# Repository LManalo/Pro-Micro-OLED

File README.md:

# Pro-Micro-OLED
An Atmega32u4-based development board with an onboard OLED display connected to pins D2-D7 and the I2C bus.

Designed during my time at Sparkfun Electronics, and the board design is based off the Sparkfun Pro Micro and Lilypad Arduino USB.

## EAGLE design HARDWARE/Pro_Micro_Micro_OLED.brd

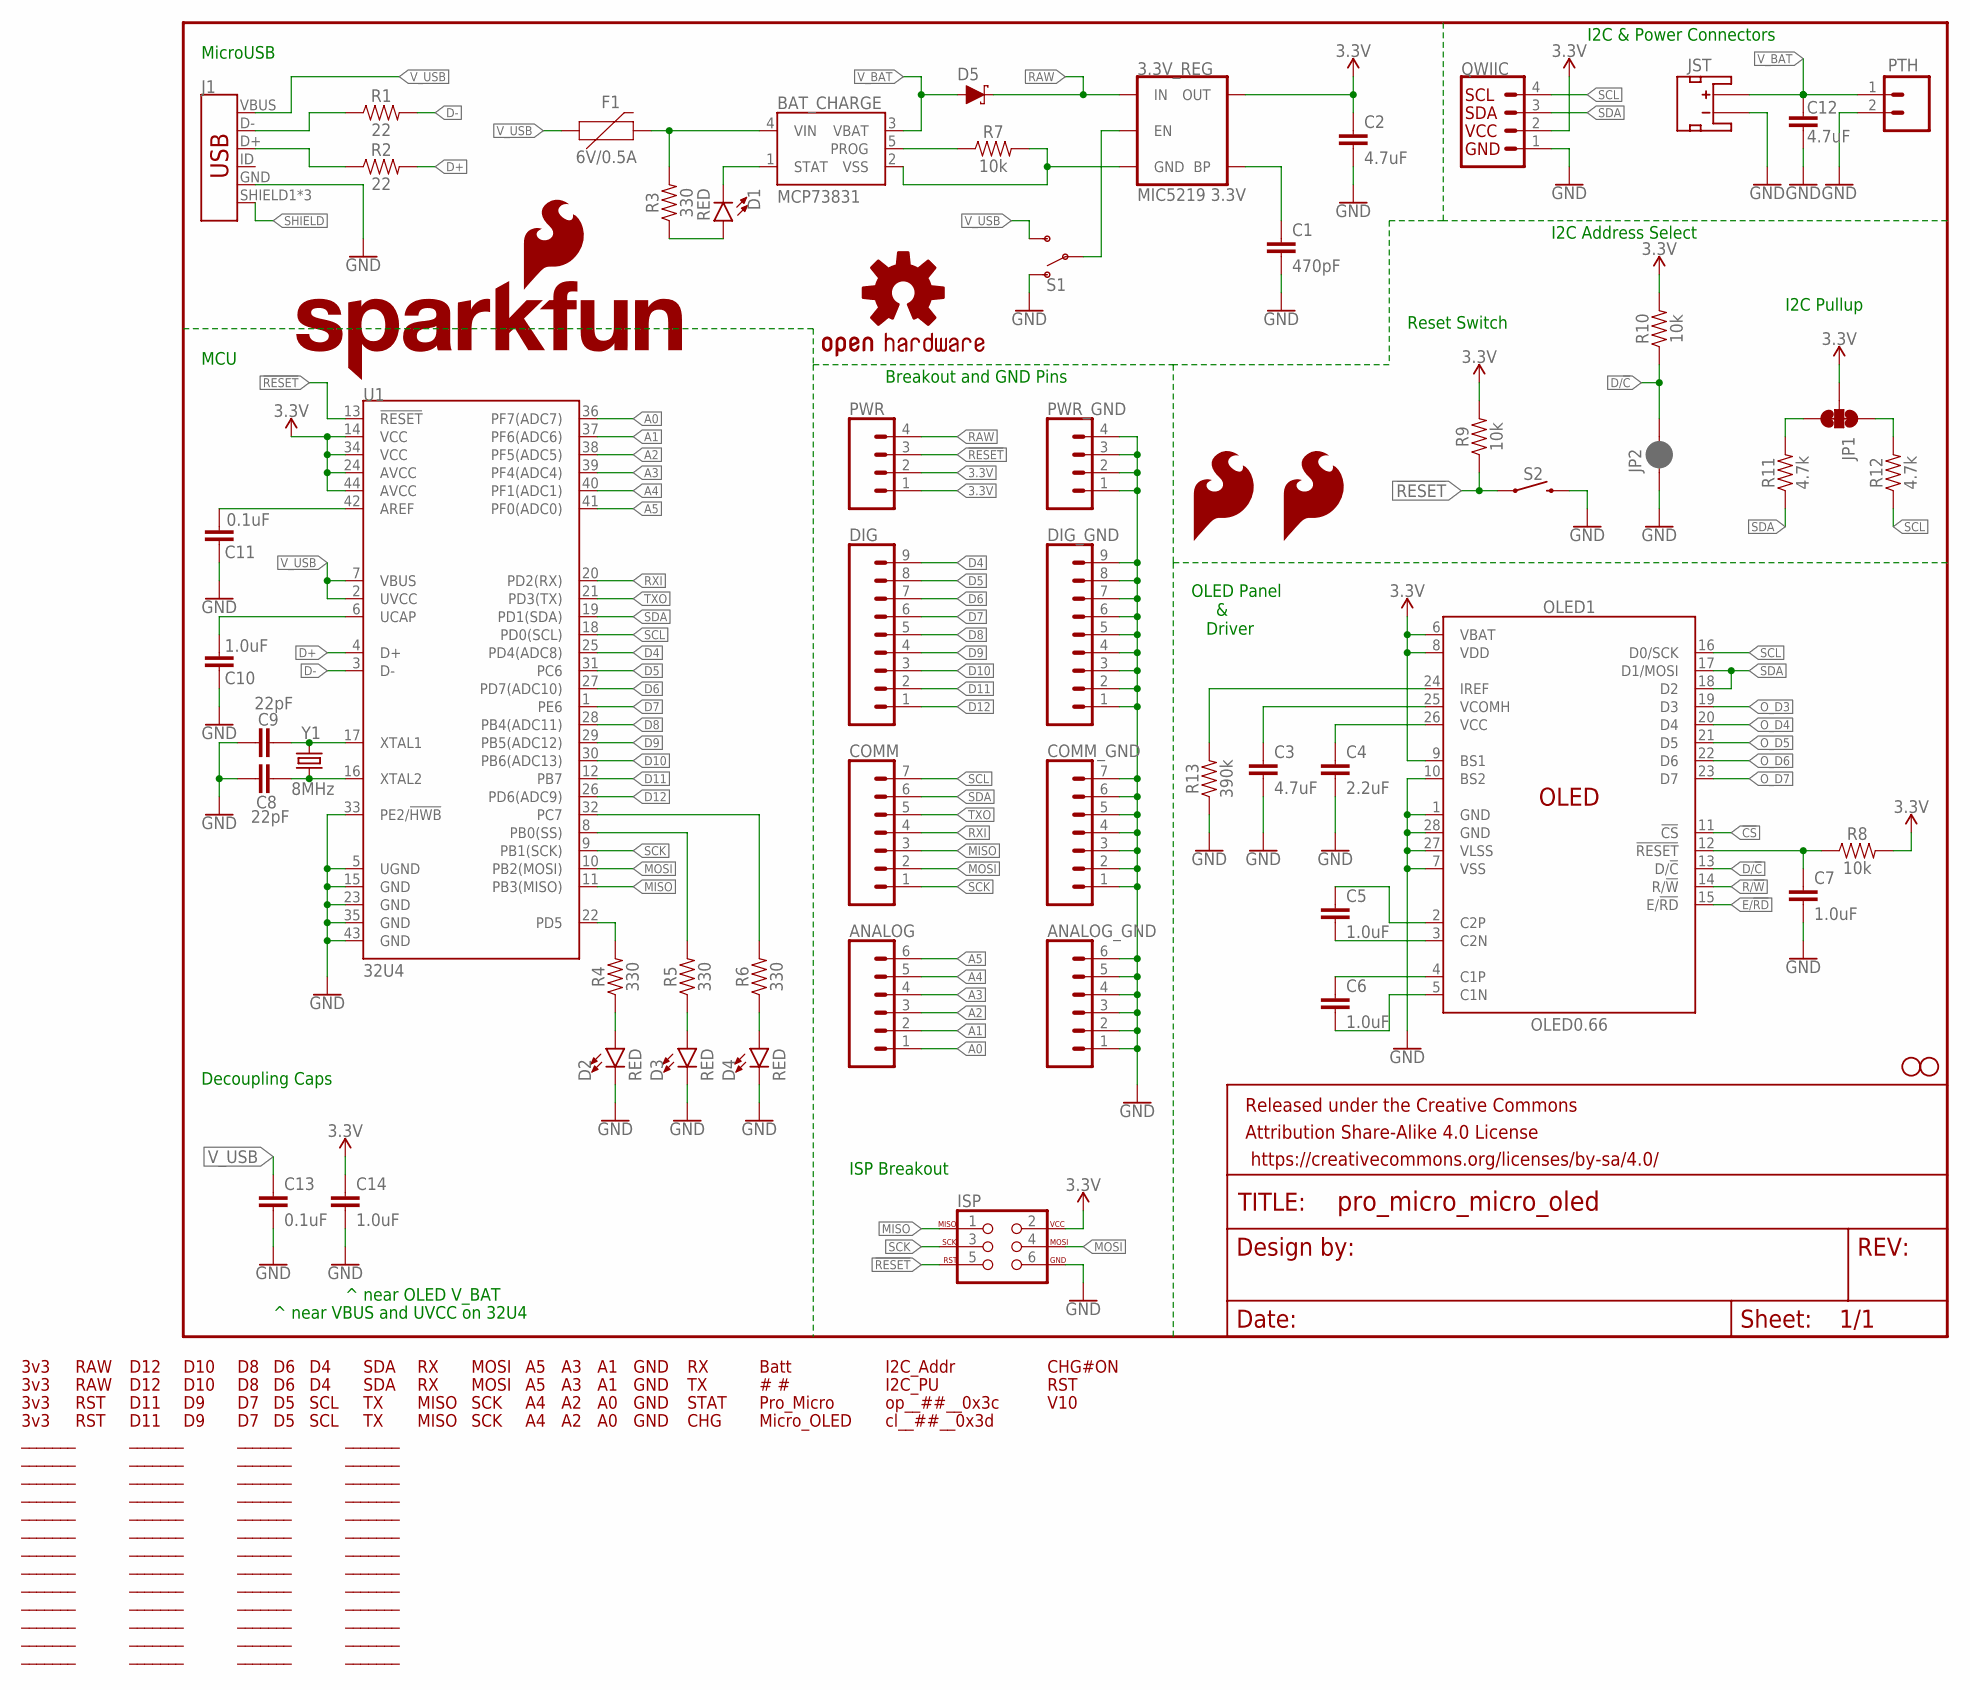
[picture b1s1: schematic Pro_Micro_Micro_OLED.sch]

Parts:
3.3V_REG: MIC5219 3.3V; SOT23-5
ANALOG: CONN_06NO_SILK_FEMALE_PTH; 1X06_NO_SILK
ANALOG_GND: CONN_06NO_SILK_FEMALE_PTH; 1X06_NO_SILK
BAT_CHARGE: MCP73831; SOT23-5
C1: 470pF; 0603
C2, C3, C12: 4.7uF; 1206
C4: 2.2uF; 0805
C5, C6: 1.0uF; 0805
C7, C10, C14: 1.0uF; 0603
C8, C9: 22pF; 0603
C11, C13: 0.1uF; 0603
COMM: CONN_07NO_SILK; 1X07_NO_SILK
COMM_GND: CONN_07NO_SILK; 1X07_NO_SILK
D1, D2, D3, D4: RED; LED-0603
D5: 3A/40V/500mV; SMA-DIODE
DIG: CONN_09NO_SILK; 1X09_NO_SILK
DIG_GND: CONN_09NO_SILK; 1X09_NO_SILK
F1: 6V/0.5A; 1206
FRAME1: FRAME-LETTER; CREATIVE_COMMONS
H1, H2: STAND-OFF
ISP: AVR_SPI_PROG_3X2TESTPOINTS; 2X3_TEST_POINTS
J1: USB_MICRO-BREDUCED_PASTE; USB-B-MICRO-SMD_RED_PASTE
JP1: JUMPER-SMT_3_2-NC_TRACE_SILK; SMT-JUMPER_3_2-NC_TRACE_SILK
JP2: JUMPER-SMT_2_NC_PASTE_SILK; SMT-JUMPER_2_NC_PASTE_SILK
JST: JST_2MM_MALE; JST-2-SMD
LOGO1: SFE_LOGO_NAME_FLAME.2_INCH; SFE_LOGO_NAME_FLAME_.2
LOGO2: OSHW-LOGOS-COPPER; OSHW-LOGO-S_COPPER
LOGO3: SFE_LOGO_FLAME.1COP; SFE_LOGO_FLAME_COPPER_.1
LOGO4: SFE_LOGO_FLAME.1_INCH; SFE_LOGO_FLAME_.1
OLED1: OLED0.66; OLED-0.66-64X48
PTH: CONN_021X02_NO_SILK; 1X02_NO_SILK
PWR: CONN_041X04_NO_SILK; 1X04_NO_SILK
PWR_GND: CONN_041X04_NO_SILK; 1X04_NO_SILK
QWIIC: QWIIC_CONNECTORJS-1MM; 1X04_1MM_RA
R1, R2: 22; 0603
R3, R4, R5, R6: 330; 0603
R7, R8, R9, R10: 10k; 0603
R11, R12: 4.7k; 0603
R13: 390k; 0603
S1: SWITCH-SPDT-SMD-RIGHT-ANGLE; SWITCH_SPST_SMD_A
S2: MOMENTARY-SWITCH-SPST-SMD-4.6X2.8MM; TACTILE_SWITCH_SMD_4.6X2.8MM
U1: 32U4; QFN-44-NOPAD_1:1
U$1, U$2, U$3, U$4: 3V317
U$5, U$6: RAW15
U$7, U$8, U$123: RST16
U$9, U$10: D120
U$11, U$12: D111
U$13, U$14: D102
U$15, U$16: D93
U$17, U$18: D84
U$19, U$20: D75
U$21, U$22: D66
U$23, U$24: D57
U$25, U$26: D48
U$27, U$28: SCL18
U$29, U$30: SDA19
U$31, U$32: TX20
U$33, U$34: RX21
U$35, U$36: MISO22
U$37, U$38: MOSI28
U$39, U$40: SCK23
U$41, U$42: A59
U$43, U$44: A410
U$45, U$46: A311
U$47, U$48: A212
U$49, U$50: A113
U$51, U$52: A014
U$53, U$54: GND38
U$55, U$56: GND39
U$57: RX36
U$58: TX34
U$59: STAT35
U$60: CHG30
U$61: BATT29
U$62: #32
U$63: #31
U$64: PRO_MICRO43
U$65: MICRO_OLED42
U$66, U$67, U$68, U$69, U$70, U$71, U$72, U$73, U$74, U$75, U$76, U$77, U$78, U$79, U$80, U$81, U$82, U$83, U$84, U$85, U$86, U$87, U$88, U$89, U$90, U$91, U$92, U$93, U$94, U$95, U$96, U$97, U$98, U$99, U$100, U$101, U$102, U$103, U$104, U$105, U$106, U$107, U$108, U$109, U$110, U$111, U$112, U$113, U$114, U$115, U$116, U$117: _______39
U$118: I2C_ADDR40
U$119: I2C_PU39
U$120: OP__##__0X3C42
U$121: CL__##__0X3D41
U$122: CHG#ON41
U$124: V1044
Y1: 8MHz; CRYSTAL-SMD-5X3.2-4PAD

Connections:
3.3V: 3.3V_REG.5 (OUT), C2.1, C14.1, ISP.2, JP1.2, OLED1.6 (VBAT), OLED1.8 (VDD), OLED1.9 (BS1), PWR.1, PWR.2, QWIIC.2, R8.2, R9.2, R10.2, U1.14 (VCC), U1.24 (AVCC), U1.34 (VCC), U1.44 (AVCC)
!CS: OLED1.11 (!CS!)
!RESET: ISP.5, PWR.3, R9.1, S2.1, S2.2 (1), U1.13 (!RESET)
A0: ANALOG.1, U1.36 (PF7(ADC7))
A1: ANALOG.2, U1.37 (PF6(ADC6))
A2: ANALOG.3, U1.38 (PF5(ADC5))
A3: ANALOG.4, U1.39 (PF4(ADC4))
A4: ANALOG.5, U1.40 (PF1(ADC1))
A5: ANALOG.6, U1.41 (PF0(ADC0))
D4: DIG.9, U1.25 (PD4(ADC8))
D5: DIG.8, U1.31 (PC6)
D6: DIG.7, U1.27 (PD7(ADC10))
D7: DIG.6, U1.1 (PE6)
D8: DIG.5, U1.28 (PB4(ADC11))
D9: DIG.4, U1.29 (PB5(ADC12))
D10: DIG.3, U1.30 (PB6(ADC13))
D11: DIG.2, U1.12 (PB7)
D12: DIG.1, U1.26 (PD6(ADC9))
D+: R2.2, U1.4 (D+)
D-: R1.2, U1.3 (D-)
D/!C: JP2.2, OLED1.13 (D/!C!), R10.1
E/!RD: OLED1.15 (E/!RD!)
GND: ANALOG_GND.1, ANALOG_GND.2, ANALOG_GND.3, ANALOG_GND.4, ANALOG_GND.5, ANALOG_GND.6, C1.2, C2.2, C3.2, C4.2, C7.2, C8.1, C9.1, C10.2, C11.2, C12.2, C13.2, C14.2, COMM_GND.1, COMM_GND.2, COMM_GND.3, COMM_GND.4, COMM_GND.5, COMM_GND.6, COMM_GND.7, D2.C, D3.C, D4.C, DIG_GND.1, DIG_GND.2, DIG_GND.3, DIG_GND.4, DIG_GND.5, DIG_GND.6, DIG_GND.7, DIG_GND.8, DIG_GND.9, ISP.6, J1.GND, JP2.1, JST.1 (-), OLED1.1 (GND), OLED1.7 (VSS), OLED1.10 (BS2), OLED1.27 (VLSS), OLED1.28 (GND), PTH.2, PWR_GND.1, PWR_GND.2, PWR_GND.3, PWR_GND.4, QWIIC.1, R13.1, S1.1 (O), S2.3 (2), S2.4 (2), U1.5 (UGND), U1.15 (GND), U1.23 (GND), U1.33 (PE2/!HWB), U1.35 (GND), U1.43 (GND)
MISO: COMM.3, ISP.1, U1.11 (PB3(MISO))
MOSI: COMM.2, ISP.4, U1.10 (PB2(MOSI))
unnamed: J1.D+, R2.1
unnamed: BAT_CHARGE.4 (VIN), F1.2, R3.2
unnamed: D1.A, R3.1
unnamed: BAT_CHARGE.1 (STAT), D1.C
unnamed: BAT_CHARGE.5 (PROG), R7.1
unnamed: 3.3V_REG.4 (BP), C1.1
unnamed: 3.3V_REG.2 (GND), BAT_CHARGE.2 (VSS), R7.2
unnamed: C9.2, U1.17 (XTAL1), Y1.3 (2)
unnamed: 3.3V_REG.3 (EN), S1.2
unnamed: J1.D-, R1.1
unnamed: C11.1, U1.42 (AREF)
unnamed: C10.1, U1.6 (UCAP)
unnamed: C7.1, OLED1.12 (!RESET!), R8.1
unnamed: C8.2, U1.16 (XTAL2), Y1.1
unnamed: C4.1, OLED1.26 (VCC)
unnamed: C3.1, OLED1.25 (VCOMH)
unnamed: R4.2, U1.22 (PD5)
unnamed: R5.2, U1.8 (PB0(SS))
unnamed: R6.2, U1.32 (PC7)
unnamed: D2.A, R4.1
unnamed: D3.A, R5.1
unnamed: D4.A, R6.1
unnamed: OLED1.24 (IREF), R13.2
unnamed: C5.2, OLED1.3 (C2N)
unnamed: C5.1, OLED1.2 (C2P)
unnamed: C6.1, OLED1.4 (C1P)
unnamed: C6.2, OLED1.5 (C1N)
unnamed: JP1.1, R12.2
unnamed: JP1.3, R11.2
O_D3: OLED1.19 (D3)
O_D4: OLED1.20 (D4)
O_D5: OLED1.21 (D5)
O_D6: OLED1.22 (D6)
O_D7: OLED1.23 (D7)
R/!W: OLED1.14 (R/!W!)
RAW: 3.3V_REG.1 (IN), D5.C, PWR.4
RXI: COMM.4, U1.20 (PD2(RX))
SCK: COMM.1, ISP.3, U1.9 (PB1(SCK))
SCL: COMM.7, OLED1.16 (D0/SCK), QWIIC.4, R12.1, U1.18 (PD0(SCL))
SDA: COMM.6, OLED1.17 (D1/MOSI), OLED1.18 (D2), QWIIC.3, R11.1, U1.19 (PD1(SDA))
SHIELD: J1.SHIELD1 (SHIELD), J1.SHIELD2 (SHIELD), J1.SHIELD3 (SHIELD)
TXO: COMM.5, U1.21 (PD3(TX))
V_BAT: BAT_CHARGE.3 (VBAT), C12.1, D5.A, JST.2 (+), PTH.1
V_USB: C13.1, F1.1, J1.VBUS, S1.3 (S), U1.2 (UVCC), U1.7 (VBUS)

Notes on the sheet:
^ near OLED V_BAT
^ near VBUS and UVCC on 32U4
OLED Panel & Driver
Reset Switch
I2C Address Select
I2C Pullup
I2C & Power Connectors
Breakout and GND Pins
ISP Breakout
MCU
Decoupling Caps
MicroUSB

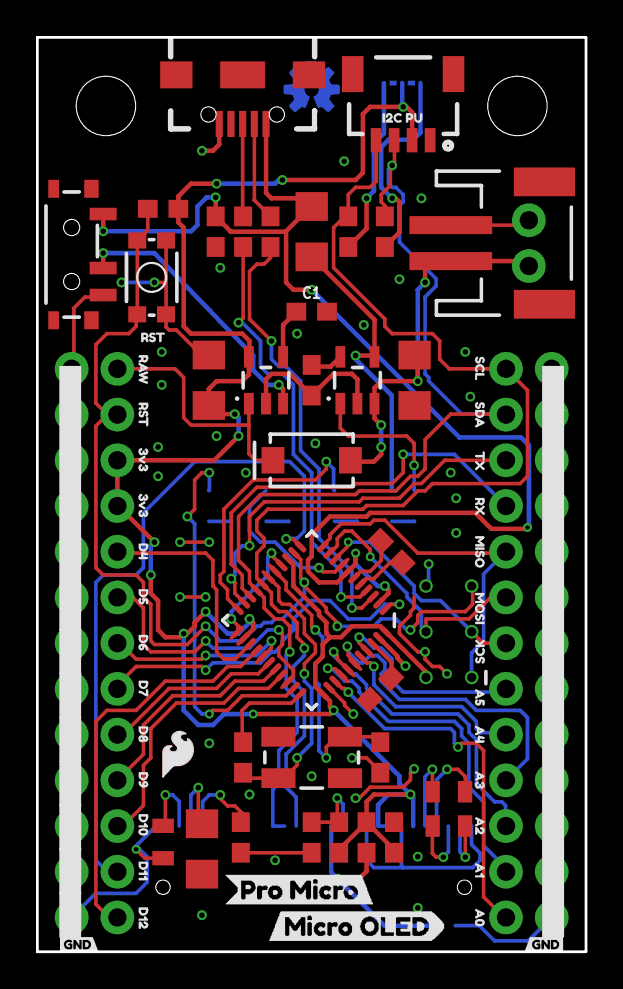
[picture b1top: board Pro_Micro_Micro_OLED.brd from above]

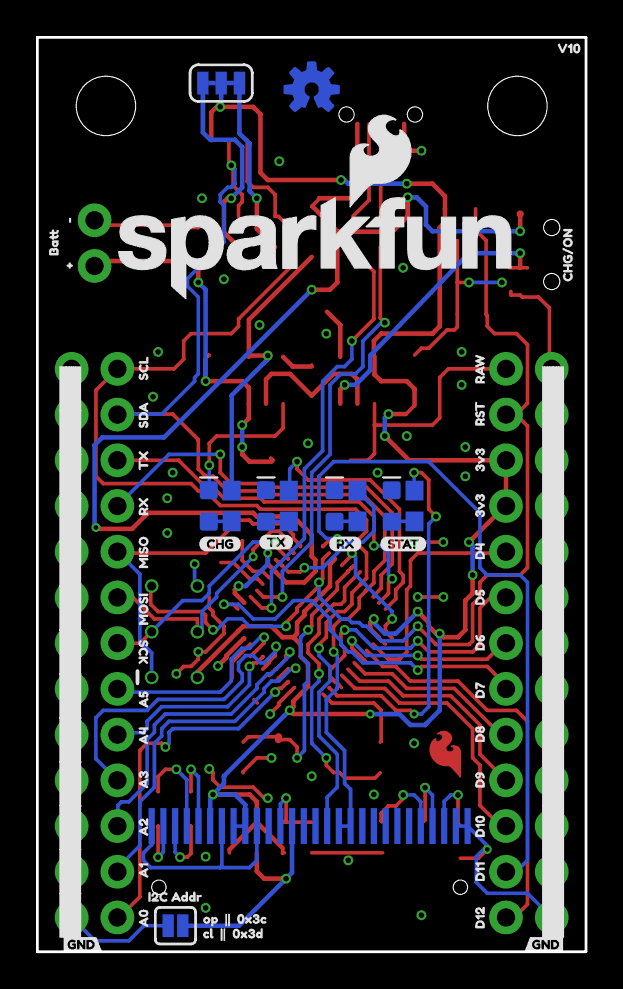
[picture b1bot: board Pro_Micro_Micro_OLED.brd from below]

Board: 2 copper layers, 30.5 x 50.8 mm, 186 parts (79 on the bottom side), 61 nets.

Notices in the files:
parts and their libraries:
SparkFun-Aesthetics: Licensing: Creative Commons ShareAlike 4.0 International - https://creativecommons.org/licenses/by-sa/4.0
SparkFun-Aesthetics: Released under the Creative Commons Attribution Share-Alike 4.0 License
SparkFun-Aesthetics: https://creativecommons.org/licenses/by-sa/4.0
